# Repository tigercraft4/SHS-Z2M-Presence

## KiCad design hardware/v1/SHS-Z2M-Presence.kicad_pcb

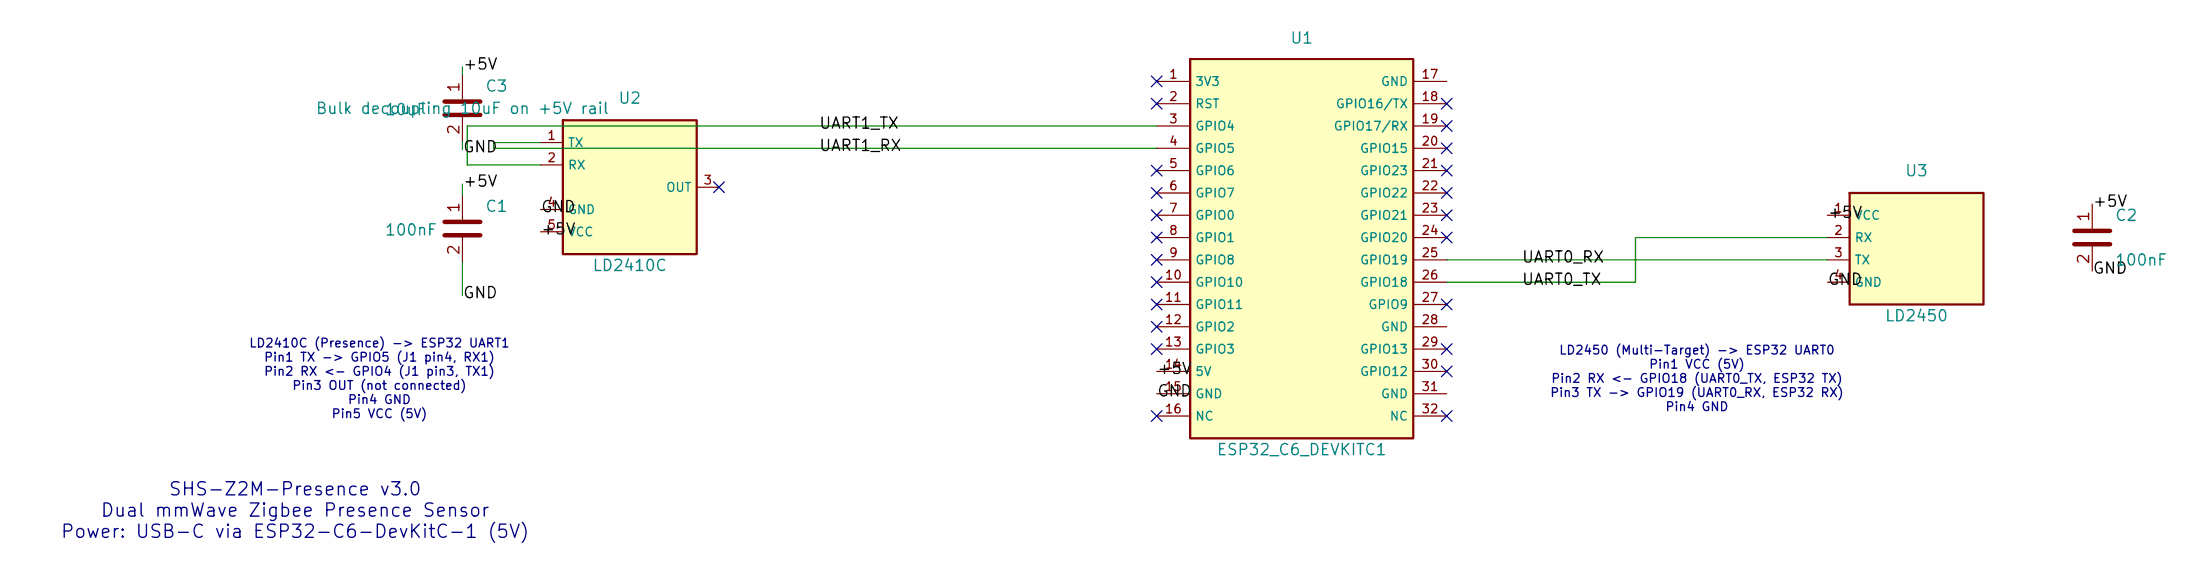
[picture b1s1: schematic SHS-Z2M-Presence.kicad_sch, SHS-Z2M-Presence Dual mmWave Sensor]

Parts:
C1, C2: 100nF; C_0805_2012Metric; MPN CL21B104KACNNNC
C3: 10uF; C_0805_2012Metric; MPN GRM21BR61A106KE18L
U1: ESP32_C6_DEVKITC1; MPN ESP32-C6-DEVKITC-1-N8
U2: LD2410C; MPN LD2410C
U3: LD2450; MPN LD2450

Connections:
+5V: C1.1, C2.1, C3.1, U1.14 (5V), U2.5 (VCC), U3.1 (VCC)
GND: C1.2, C2.2, C3.2, U1.15 (GND), U1.17 (GND), U1.28 (GND), U1.31 (GND), U2.4 (GND), U3.4 (GND)
UART0_RX: U1.25 (GPIO19), U3.3 (TX)
UART0_TX: U1.26 (GPIO18), U3.2 (RX)
UART1_RX: U1.3 (GPIO4), U2.2 (RX)
UART1_TX: U1.4 (GPIO5), U2.1 (TX)

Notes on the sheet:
SHS-Z2M-Presence v3.0 Dual mmWave Zigbee Presence Sensor Power: USB-C via ESP32-C6-DevKitC-1 (5V)
LD2410C (Presence) -> ESP32 UART1 Pin1 TX -> GPIO5 (J1 pin4, RX1) Pin2 RX <- GPIO4 (J1 pin3, TX1) Pin3 OUT (not connected) Pin4 GND Pin5 VCC (5V)
LD2450 (Multi-Target) -> ESP32 UART0 Pin1 VCC (5V) Pin2 RX <- GPIO18 (UART0_TX, ESP32 TX) Pin3 TX -> GPIO19 (UART0_RX, ESP32 RX) Pin4 GND

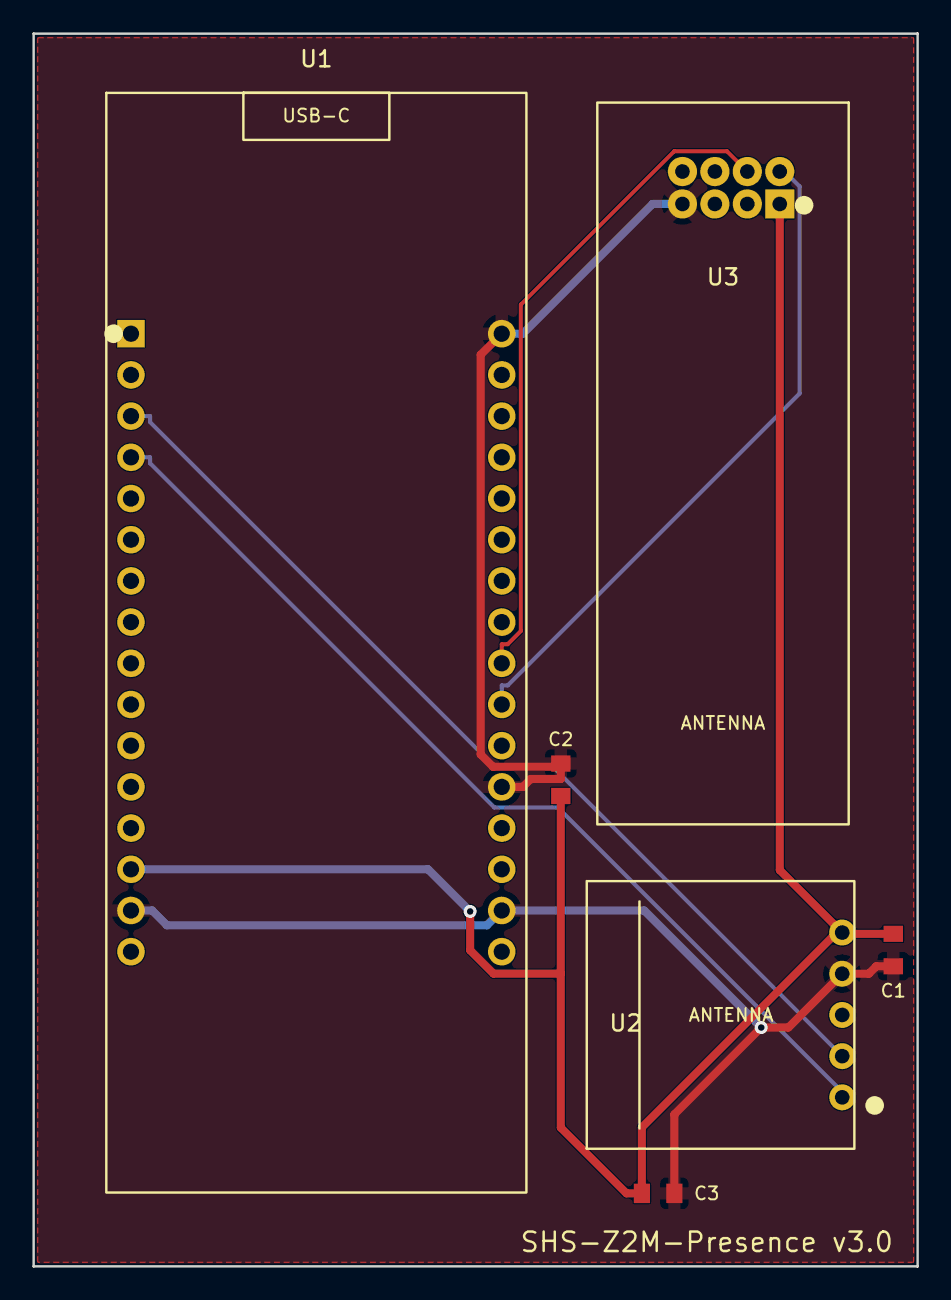
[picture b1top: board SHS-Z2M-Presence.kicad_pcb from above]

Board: 2 copper layers, 54.5 x 76.0 mm, 6 parts (0 on the bottom side), 6 nets.

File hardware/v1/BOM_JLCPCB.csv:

Comment,Designator,Footprint,LCSC Part #
100nF,C1 C2,C_0805_2012Metric,C28233
10uF,C3,C_0805_2012Metric,C15850

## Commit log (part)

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2026-04-30 chore: add project config
2026-04-30 docs: initialize project
2026-04-30 docs: complete project research
2026-04-30 docs: define v1 requirements
2026-04-30 docs: create v1 roadmap (4 phases, 24 requirements mapped)
2026-04-30 docs(01): capture phase context
2026-04-30 docs(01): create phase plan (2 plans, 2 waves)
2026-04-30 fix(01-01): add zone_config_mutex and volatile position_reporting
    - Declare zone_config_mutex after target_data_mutex
    - Initialize zone_config_mutex in app_main before task creation
    - Mark shs_position_reporting as volatile for atomic single-core access
2026-04-30 fix(01-01): protect shs_ld2450_target_count with target_data_mutex
    - Read target count under mutex in shs_on_state_change cross-validation
    - Read/write target count under mutex in shs_on_ld2450_target_update
    - No nested mutex takes — each take/give is self-contained
    - Mutex not held during Zigbee lock calls to avoid priority inversion
2026-04-30 fix(01-01): protect zone config variables with zone_config_mutex
    - Wrap all 31 zone attribute writes in Zigbee handler with zone_config_mutex
    - Copy zone vars to locals under mutex in shs_zone_cfg_apply_to_sensor
    - Prevents partial zone config reads during concurrent Zigbee attribute updates
    - Mutex timeout returns early with warning log (no deadlock risk)
2026-04-30 docs(01-01): add plan summary
2026-04-30 fix(01-02): replace Zigbee lock macros with retry + exponential backoff
    - 3 attempts with backoff: 50ms, 100ms, 200ms (350ms total max wait)
    - Both RETURN and RETURN_FALSE variants have retry loop
    - Log message updated to 'FAILED after 3 retries' for clarity
    - Kept SHS_ZB_LOCK_TIMEOUT_MS for one-off lock acquire in boot button handler
2026-04-30 fix(01-02): route zone NVS saves through save_worker task
    - Add SHS_SAVE_ZONE_CONFIG to save event enum
    - Replace direct shs_zone_cfg_save_to_nvs() call with shs_save_enqueue()
    - Add case handler in shs_save_worker for zone config saves
    - NVS writes now happen at priority 3 instead of blocking sensor/Zigbee callbacks
2026-04-30 docs(01-02): add plan summary
2026-04-30 docs: update STATE.md and ROADMAP.md for Phase 1 completion
2026-04-30 docs(02): create phase plan for sensor filters and converter fix
2026-04-30 feat(02-01): re-enable EMA smoothing at alpha=0.3 and reduce rate limit to 200ms
2026-04-30 feat(02-01): add LD2410C standalone filter when LD2450 disconnected
2026-04-30 feat(02-01): remove +3000 X coordinate bias, send raw signed values
2026-04-30 docs(02-01): create plan summary
2026-04-30 docs(phase-02): update tracking after wave 1
2026-04-30 feat(02-02): remove X coordinate bias subtraction from JS converter
2026-04-30 feat(02-02): remove X coordinate bias subtraction from MJS converter
2026-04-30 docs(02-02): create plan summary
2026-04-30 docs(phase-02): update tracking after wave 2
2026-04-30 docs(phase-02): complete phase execution — verification passed
2026-04-30 docs(03): capture phase context
2026-04-30 docs(state): record phase 3 context session
2026-04-30 docs(03): create phase 3 reliability & diagnostics plans
2026-04-30 feat(03-01): add task watchdog + LD2410C frame disconnect detection
    - Enable ESP-IDF TWDT with 10s timeout and panic-on-trigger
    - Subscribe both sensor tasks (ld2410, ld2450) to TWDT
    - Add esp_task_wdt_reset() in both sensor task loops
    - Add LD2410C frame timestamp tracking with 3s disconnect threshold
    - Disable idle task monitoring (single-core ESP32-C6 may starve under Zigbee)
2026-04-30 feat(03-01): NVS zone config atomic blob + error logging
    - Replace 31 individual NVS writes with single nvs_set_blob (51 bytes)
    - Add shs_zone_cfg_blob_t packed struct for atomic save
    - Load tries blob first, falls back to legacy per-key format
    - Legacy configs auto-migrate to blob on first boot
    - Add ESP_LOGW to NVS helper functions on open failure
2026-04-30 docs(03-01): add execution summary
2026-04-30 feat(03-02): add health + diagnostic Zigbee attributes on 0xFDCD
    - Define 9 new attributes in shs01.h (0x0070-0x0071, 0x0080-0x0086)
    - Register on config cluster EP1 as read-only with reporting
    - Add shs_zb_report_sensor_health() for LD2410C/LD2450 connected status
    - Add shs_zb_report_diagnostics() for lock/TX counters + uptime + heap
    - Report health on LD2450 connect/disconnect events
    - Report health + diagnostics every 60s in periodic check
2026-04-30 feat(03-02): add Z2M converter decode for health + diagnostic attributes
    - Add 9 attribute constants (0x0070-0x0071, 0x0080-0x0086) to both .js and .mjs
    - Add fromZigbee decode for health booleans and diagnostic counters
    - Add exposes: 2 binary (sensor connected) + 7 numeric (lock/TX/uptime/heap)
    - Add configure read for initial attribute values on interview
    - Both .js and .mjs files updated identically
2026-04-30 docs(03-02): add execution summary
2026-04-30 docs(phase-3): complete phase execution — reliability & diagnostics
2026-04-30 docs(04): capture phase context
2026-04-30 docs(state): record phase 4 context session
2026-04-30 docs(04): create phase plan — 3 plans in 3 waves
2026-04-30 feat(04-01): create shared state struct (shs_state.h/c)
2026-04-30 docs(04-01): add plan summary
2026-04-30 feat(04-02): create Zigbee module with endpoint factories (shs_zigbee.h/c)
2026-04-30 docs(04-02): add plan summary
2026-04-30 refactor(04-03): split shs01.c into config/sensor/button modules, slim app_main
    - shs_config.h/c: NVS load/save, zone blob format, computed zone attr handler (CS-03), save_worker task, LD2410 config apply
    - shs_sensor.h/c: LD2410/LD2450 tasks, target callbacks, zone occupancy with loops, position smoothing, connectivity monitoring
    - shs_button.h/c: boot button task with triple/quad-click detection, factory reset, LED feedback
    - shs01.c: 85-line app_main — NVS init, state init, module inits, driver inits, 5x xTaskCreate
    - shs01.h: added shared constants (ZB lock timeout, button timing, LD2410C frame timeout)
    - shs_zigbee.h/c: added shs_zb_schedule_rejoin(), removed duplicate SHS_ZB_LOCK_TIM
2026-04-30 docs(04-03): add phase 03 execution summary
2026-04-30 docs(04): mark Phase 4 complete, update project state to 100%
2026-05-04 fix: ESP-IDF v6.0.1 build compatibility
    - Add esp_driver_uart to ld2410_enhanced deps
    - Add esp_driver_uart/gpio to ld2450 deps
    - Cast volatile bool* to void* for ZB API calls (GCC 15 -Werror=discarded-qualifiers)
    - Add const to zcl_utility manufacturer_info param
